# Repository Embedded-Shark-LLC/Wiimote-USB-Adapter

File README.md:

# Wiimote-USB-Adapter
This is a Wiimote adapter to wirelessly connect remotes for Dolphin or other emulators through a USB-C connection to a computer.

Includes support for sensor bar USB passthrough (power only) or external infrared LEDs to act as a standalone sensor bar.

## Features
- USB-C power/data input
- USB-A port for external sensor bars

## Concept
I wanted a way to connect Wiimotes to a computer without the overhead of third-party Bluetooth adapters.  This uses the OEM Wiimote Bluetooth module, so there is minimal latency and no weird syncing issues.

## Planned Features
- Enclosure with support for integrated IR LEDs to act as a standalone sensor bar

## PCB Renders
|PCB Front|PCB Back|
|---------|--------|
|||

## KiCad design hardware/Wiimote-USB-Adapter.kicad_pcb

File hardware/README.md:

# Hardware

## Major components
| Description           | Part Number           | Manufacturer          | Comments                          |
| --------------------- | --------------------- | --------------------- | --------------------------------- |
| Bluetooth module      | J27H002               | Foxconn               | OEM Wiimote BT module             |
| Voltage regulator     | LM1117MPX-3.3/NOPB    | Texas Instruments     | 3.3 V, 800 mA                     |
| USB A port            | GSB12121RSKEU         | Amphenol              | THT, right angle                  |
| USB C port            | GSB1C211110DS1HR      | Amphenol              | THT, USB 2.0, right angle         |
| Sync button           | PTS645SM50SMTR92 LFS  | C&K                   | SMD, vertical                     |

## Minor components
| Description           | Part Number           | Manufacturer          | Comments                          |
| --------------------- | --------------------- | --------------------- | --------------------------------- |
| Resettable fuse       | SMD1206B050TF/15      | YAGEO                 | 500 mA hold, 1 A trip, 15 V max   |

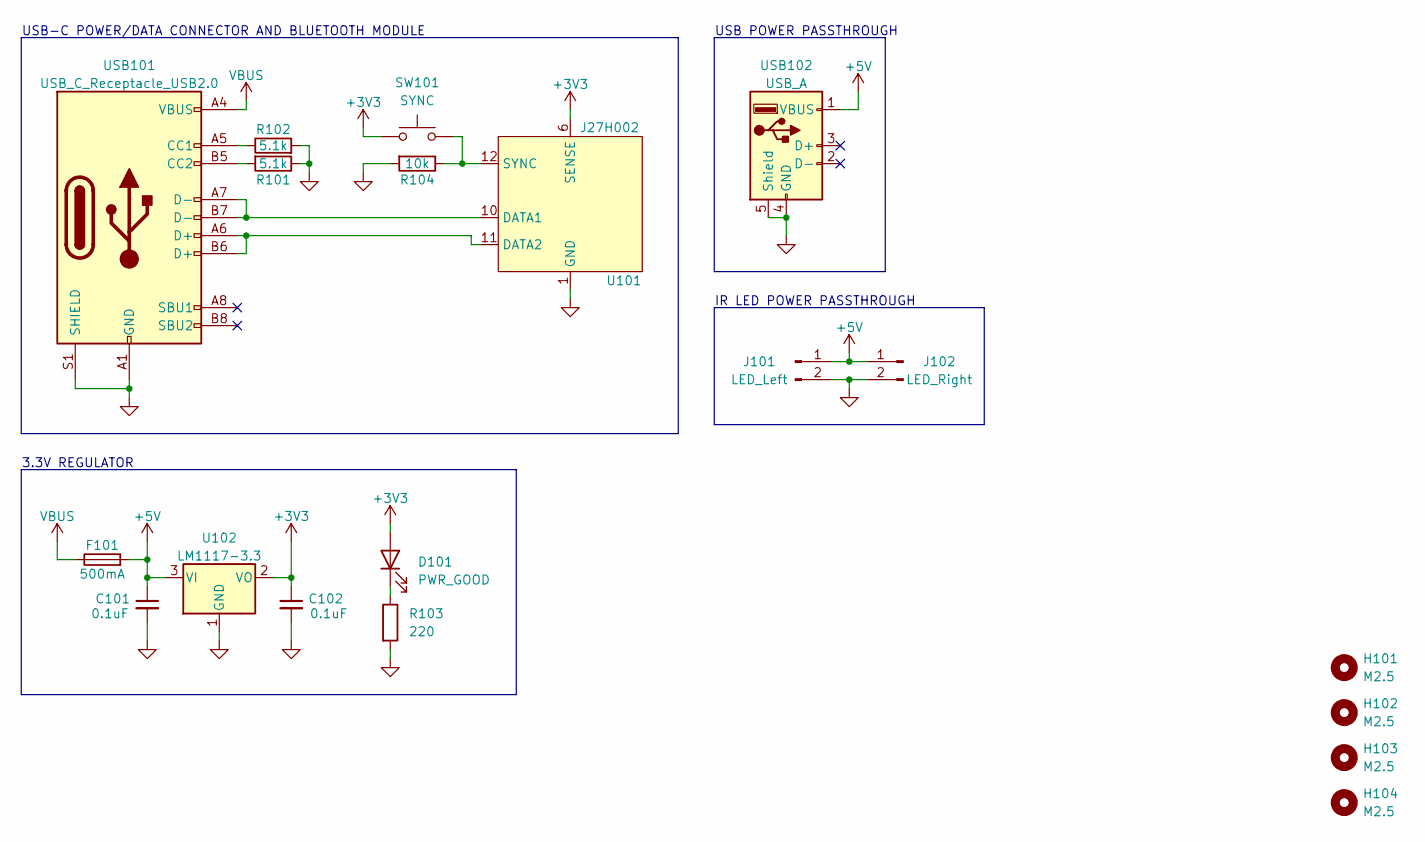
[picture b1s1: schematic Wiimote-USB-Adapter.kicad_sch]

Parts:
C101, C102: 0.1uF; C_0805_2012Metric_Pad1.18x1.45mm_HandSolder
D101: PWR_GOOD; LED_D3.0mm
F101: 500mA; Fuse_1206_3216Metric_Pad1.42x1.75mm_HandSolder
H101, H102, H103, H104: M2.5; MountingHole_2.7mm_M2.5
J101: LED_Left; PinHeader_1x02_P2.54mm_Vertical
J102: LED_Right; PinHeader_1x02_P2.54mm_Vertical
R101, R102: 5.1k; R_0805_2012Metric_Pad1.20x1.40mm_HandSolder
R103: 220; R_0805_2012Metric_Pad1.20x1.40mm_HandSolder
R104: 10k; R_0805_2012Metric_Pad1.20x1.40mm_HandSolder
SW101: SYNC; SW_SPST_PTS645
U101: J27H002
U102: LM1117-3.3; SOT-223-3_TabPin2
USB101: USB_C_Receptacle_USB2.0; GSB1C211110DS1HR
USB102: USB_A; USB_A_Molex_67643_Horizontal

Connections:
+3V3: C102.1, D101.2 (A), SW101.1, U101.6 (SENSE), U101.7 (SENSE), U101.13 (SENSE), U102.2 (VO)
+5V: C101.1, F101.2, J101.1, J102.1, U102.3 (VI), USB102.1 (VBUS)
GND: C101.2, C102.2, J101.2, J102.2, R101.1, R102.2, R103.2, R104.2, U101.1 (GND), U101.8 (GND), U101.9 (GND), U101.16 (GND), U102.1 (GND), USB101.A1 (GND), USB101.A12 (GND), USB101.B1 (GND), USB101.B12 (GND), USB101.S1 (SHIELD), USB102.4 (GND), USB102.5 (Shield)
unnamed: D101.1 (K), R103.1
unnamed: U101.10 (DATA1), USB101.A7 (D-), USB101.B7 (D-)
unnamed: U101.11 (DATA2), USB101.A6 (D+), USB101.B6 (D+)
unnamed: R104.1, SW101.2, U101.12 (SYNC)
unnamed: R102.1, USB101.A5 (CC1)
unnamed: R101.2, USB101.B5 (CC2)
VBUS: F101.1, USB101.A4 (VBUS), USB101.A9 (VBUS), USB101.B4 (VBUS), USB101.B9 (VBUS)

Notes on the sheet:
USB POWER PASSTHROUGH
3.3V REGULATOR
USB-C POWER/DATA CONNECTOR AND BLUETOOTH MODULE
IR LED POWER PASSTHROUGH

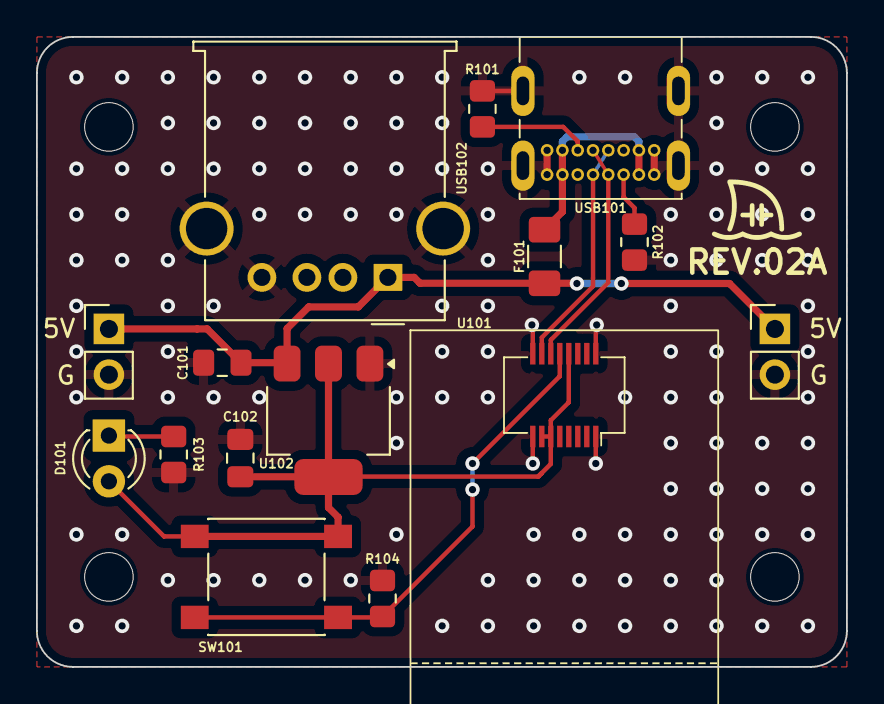
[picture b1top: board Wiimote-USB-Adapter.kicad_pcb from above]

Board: 2 copper layers, 45.0 x 35.0 mm, 19 parts (0 on the bottom side), 10 nets.

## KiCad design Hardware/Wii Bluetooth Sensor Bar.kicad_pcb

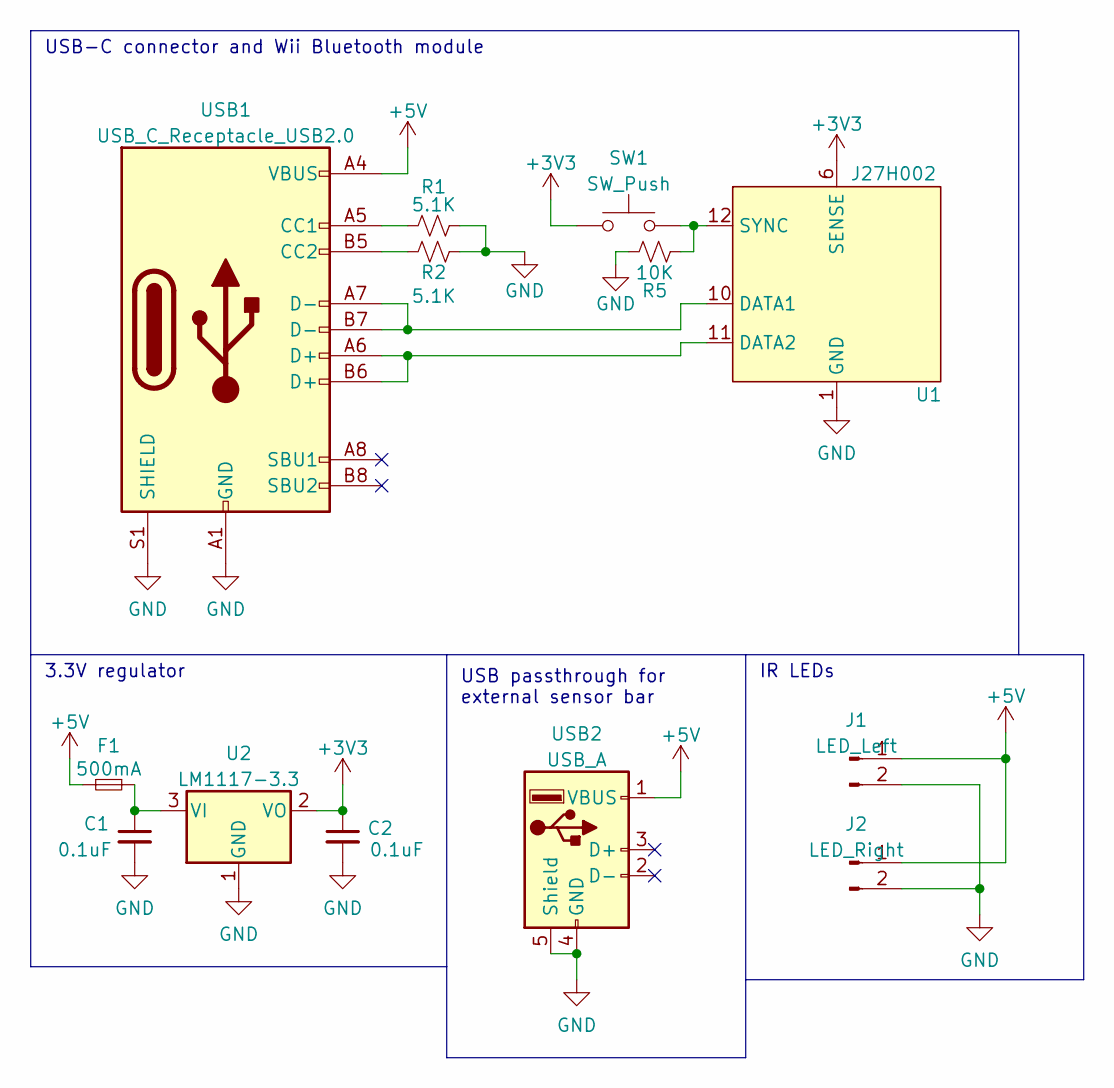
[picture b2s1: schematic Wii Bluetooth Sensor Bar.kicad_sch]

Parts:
C1, C2: 0.1uF; C_0805_2012Metric_Pad1.18x1.45mm_HandSolder
F1: 500mA; Fuse_0805_2012Metric_Pad1.15x1.40mm_HandSolder
J1: LED_Left; PinHeader_1x02_P2.54mm_Vertical
J2: LED_Right; PinHeader_1x02_P2.54mm_Vertical
R1, R2: 5.1K; R_0805_2012Metric_Pad1.20x1.40mm_HandSolder
R5: 10K; R_0805_2012Metric_Pad1.20x1.40mm_HandSolder
SW1: SW_Push; SW_SPST_PTS645
U1: J27H002
U2: LM1117-3.3; SOT-223-3_TabPin2
USB1: USB_C_Receptacle_USB2.0; USB_C_Receptacle_Amphenol_C12402012
USB2: USB_A; USB_A_Molex_67643_Horizontal

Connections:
+3V3: C2.1, SW1.1, U1.6 (SENSE), U1.7 (SENSE), U1.13 (SENSE), U2.2 (VO)
+5V: F1.1, J1.1, J2.1, USB1.A4 (VBUS), USB1.A9 (VBUS), USB1.B4 (VBUS), USB1.B9 (VBUS), USB2.1 (VBUS)
GND: C1.2, C2.2, J1.2, J2.2, R1.2, R2.2, R5.2, U1.1 (GND), U1.8 (GND), U1.9 (GND), U1.16 (GND), U2.1 (GND), USB1.A1 (GND), USB1.A12 (GND), USB1.B1 (GND), USB1.B12 (GND), USB1.S1 (SHIELD), USB2.4 (GND), USB2.5 (Shield)
unnamed: C1.1, F1.2, U2.3 (VI)
unnamed: R1.1, USB1.A5 (CC1)
unnamed: R2.1, USB1.B5 (CC2)
unnamed: U1.10 (DATA1), USB1.A7 (D-), USB1.B7 (D-)
unnamed: U1.11 (DATA2), USB1.A6 (D+), USB1.B6 (D+)
unnamed: R5.1, SW1.2, U1.12 (SYNC)

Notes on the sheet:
USB passthrough for external sensor bar
3.3V regulator
USB-C connector and Wii Bluetooth module
IR LEDs

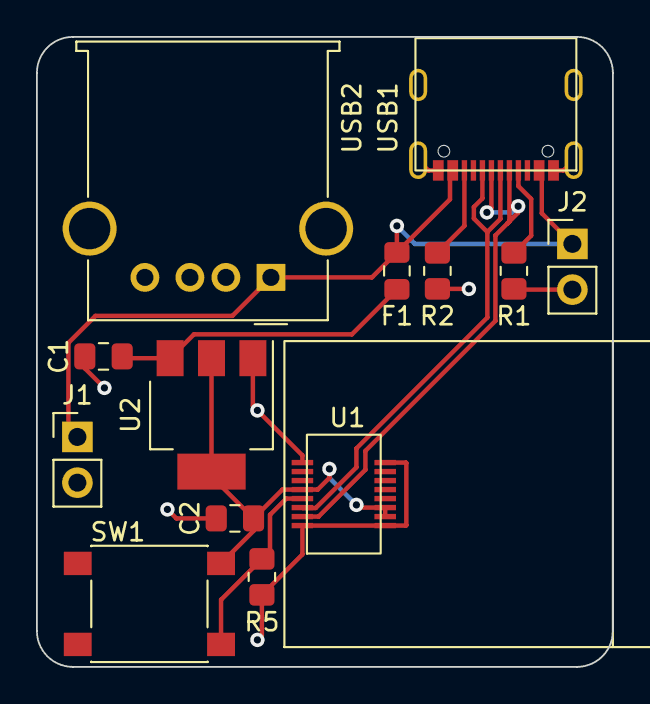
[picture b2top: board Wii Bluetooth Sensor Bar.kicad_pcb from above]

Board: 2 copper layers, 32.0 x 35.0 mm, 13 parts (0 on the bottom side), 9 nets.

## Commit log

2022-06-30 Add schematic and begin footprint association
2022-07-04 Finish footprint assignment and rough PCB layout
2022-07-06 Finish Rev A PCB
2022-07-06 Add HTML BOM
2022-07-06 Add 3D models for some components (not accurate)
2022-07-06 Fix reversed bluetooth module connector
2022-07-09 Fix incorrect sync button footprint
2022-07-09 Add PCB label text
2022-07-27 Fix #1
2022-07-28 Fix #2
2022-07-28 Update terminology
2022-08-02 Add Ben's Universe logo #3
2022-08-02 Update gitignore for KiCad 6
2022-08-02 KiCad 6 cleanup
2022-08-02 Update versioning
2022-08-02 Delete Hardware/Wii Bluetooth Sensor Bar-backups directory
    KiCad 6 cleanup
2022-08-03 Add FreeCAD files to gitignore
2022-08-03 Create enclosure model (not finished)
2022-08-03 First draft of enclosure base (added port holes)
2022-08-04 Fix missing threaded insert hole, antenna overhang
2022-08-04 Increase wall thickness and add supports
2022-08-04 Remove STLs folder
2022-08-04 Add enclosure lid
2022-08-04 Add button extension
2022-08-04 Add STL files
2022-08-04 Fix physical antenna interference
2022-08-04 Fix port hole sizes and button extension length
2022-08-05 Increase USB-C port hole
2022-08-05 Enlarge USB-C port
2022-08-05 Add 3D printing suggestions
2022-08-05 Raise USB-A port hole
2022-08-05 Update 3D printing instructions
2022-08-06 Make button extension longer
2022-08-06 Make countersunk screw hole deeper
2022-08-18 Fix bad pulldown resistor
2022-08-18 Update new sync button placement
2024-09-01 Add submodule and clean up repository
2024-09-01 Update schematic/PCB
2024-09-01 Remove old enclosure files
2024-09-01 Add 3D model for J27H002 and drawings
2024-09-01 Change project name
2024-09-01 Add production files
2024-09-02 Ignore FreeCAD backup files
2024-09-02 Add more dimensions
2024-09-02 First draft of new enclosure body
2024-09-14 Update libraries
2024-09-14 Clean up silkscreen and vias
2024-09-14 Update DRC exclusions
2024-09-15 Create LICENSE
2024-11-23 Update libs
2024-11-23 Ignore production files
2024-11-23 Remove PCB markings
